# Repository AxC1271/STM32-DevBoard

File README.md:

# STM32 MCU Board

## 📖 Introduction
This repository is my first ever PCB design project. After working on projects that involved more digital circuits and RTL scripting, I've always wanted to build my own boards, specifically FPGA boards. However, I want to start on something simpler so I can understand the inner workings of PCB design, decision choices, and general concepts that are crucial to a functional STM32 board.

## 🛠️ Design Approach
Given that this is just a basic guide to designing, laying out, and manufacturing a simple STM32 board, this PCB will only offer a single USB port, an I2C interface, an SWD interface, and a UART interface. The specific processor chip that we are using is the STM32F103C8Tx, which uses an `ARM Cortex-M3 processor`. 

### ⚡ Power Regulator Circuit

<p align="center">
    <em> LDO-Based Power Regulator Circuit.</em>
</p>

Here we have the external USB-B micro port that interfaces with our STM32 microcontroller. In order to use `VBUS` coming from this port, I stepped down any input voltage down to 3.3V using the **AMS1117** chip, which requires two `22uF` capacitors according to its datasheet, one at the input and one at the output. At the output, the 3.3V signal is then passed through an LED with a current limiting resistor as a visual indicator that the 3.3V source is present at the output.

<br />
Quick note about the shield option being ignored, generally the shield pin is to connect the board to an external chassis but because this is a standalone board, that's why it's ignored.

### 🔲 STM32F103C8T6 MCU

<p align="center">
    <em>MCU Schematic with USB-B Micro Interface.</em>
</p>

First and foremost, there needs to be capacitors between the 3.3V source and ground. Since this specific STM32 microcontroller has 4 **VDD** pins, there must generally be a `100 nF` capacitor in parallel for each of these pins. These capacitors act as `decoupling capacitors`, ensuring a steady voltage supply to each VDD pin. In addition, a bulk capacitor with a value of `4.7 uF` is also placed in parallel to the decoupling capacitors to handle lower-frequency current swings, while the decoupling capacitors handle the higher frequency noise and transients.

## 🧩 PCB Layout

<p align="center">
    <em> Signal traces on the STM32 board, with power traces being 0.5mm while ordinary traces are kept at 0.3mm. Vias are used for ground traces. </em>
</p>

In general, vias are used to link ground pins to the ground plane. Most signals are routed on the top copper layer, with a couple of vias used to prevent signal crossing especially with the 3.3V bus. 
A copper pour was used near the voltage regulator to create ground and power planes whilst also reducing EMI and improving signal integrity.

Quick note: to further increase the stability of a 2-layer board like this, it is recommended to add as much stitching vias as possible, on top of adding a ground pour on the top layer. This is to decrease
the distance that sensitive signals have to travel to get to ground, reducing the inductance and therefore maximizing signal integrity.

## 🖼️ 3D View

<p align="center">
    <em> Front copper layer with all signal traces and silkscreens. </em>
</p>

## 🧪 Physical Board / Functionality

After passing a design rule check on KiCAD, it's time to send the files to a PCB manufacturer to get my board assembled. For this specific board, I'm using `JLCPCB`'s services to get my board manufactured. 

<p align="center">
    <em>Manufactured Board from JLCPCB.</em>
</p>

Unfortunately, I was unable to find the USB micro-B ports for these boards, but I still want to be able to program it using an ST-Linker that I found off of Amazon for roughly `$9`. 

## 💻 Code

To test the UART interface of this STM32 board, I'll write a simple UART transceiver on my Basys3 FPGA board to interface with it.

UART Receiver:
```VHDL
library IEEE;
use IEEE.STD_LOGIC_1164.ALL;
use IEEE.NUMERIC_STD.ALL;

entity uart_rx is
    generic (
        clk_ticks: integer := 54 -- taken from (100_000_000 / 115200) / 16 = 54.25 ticks
        );
    port ( 
        clk : in STD_LOGIC;
        rst : in STD_LOGIC;
        rx : in STD_LOGIC;
        byte : out STD_LOGIC_VECTOR (7 downto 0);
        write : out STD_LOGIC
        );
end uart_rx;

architecture Behavioral of uart_rx is
    -- define internal signals here
    type rx_state is (IDLE, START, DATA, STOP); -- defined states
    signal curr_state : rx_state := IDLE; -- initial state
    
    signal baud_clk : STD_LOGIC := '0';
    signal byte_i : STD_LOGIC_VECTOR(7 downto 0) := (others => '0');
    
begin
    -- define internal processes here
    
    -- first process is a clock generator that generates an oversampled
    -- clock signal to check for the rx signal
    clk_generator : process(clk, rst) 
        variable clk_count : integer range 0 to clk_ticks := 0;
    begin 
        if rst = '1' then
            clk_count := 0;
            baud_clk <= '0';
        elsif rising_edge(clk) then
            if clk_count = clk_ticks then
                clk_count := 0;
                baud_clk <= '1'; -- set high when clk count reaches 54
            else
                clk_count := clk_count + 1;
                baud_clk <= '0';
            end if;
        end if;
    end process;
    
    -- second process handles the state machine logic
    rx_FSM : process(clk, rst) 
        variable bit_count : integer range 0 to 7 := 0; -- check for where we are in the data word
        variable bit_duration : integer range 0 to 15 := 0; -- check if a logic level has stayed steady
    begin
        if rst = '1' then
            byte_i <= (others => '0'); -- reset data bus
            curr_state <= IDLE;
            bit_count := 0;
            bit_duration := 0;
            write <= '0';
        elsif rising_edge(clk) then
            if baud_clk = '1' then
                case curr_state is
                    when IDLE =>
                        byte_i <= (others => '0');
                        bit_count := 0;
                        bit_duration := 0;
                        write <= '0';
                        -- if the rx line gets pulled low then
                        if rx = '0' then
                            curr_state <= START;
                        end if;
                    when START =>
                        write <= '0';
                        if rx = '0' then
                            if bit_duration = 7 then
                                curr_state <= DATA;
                                bit_duration := 0;
                            else
                                bit_duration := bit_duration + 1;
                            end if;
                        else
                            curr_state <= IDLE;
                        end if;
                    when DATA =>
                        write <= '0';
                        if (bit_duration = 15) then                
                                byte_i(bit_count) <= rx;     
                                bit_duration := 0;
                                if (bit_count = 7) then -- we got 8 bits             
                                    curr_state <= STOP;
                                    bit_duration := 0;
                                else
                                    bit_count := bit_count + 1;
                                end if;
                            else
                                bit_duration := bit_duration + 1;
                            end if;
                    when STOP =>
                        if (bit_duration = 15) then      
                            if rx = '1' then  -- validate stop bit is HIGH
                                byte <= byte_i;
                                write <= '1';    
                                curr_state <= IDLE;
                            else
                            -- Invalid stop bit, frame error - reset
                                curr_state <= IDLE;
                            end if;
                        else
                            bit_duration := bit_duration + 1;
                        end if;
                    when others =>
                        curr_state <= IDLE;
                end case;
            end if;
        end if;
    end process;

end Behavioral;
```

Now we can write the C++ code for the STM32 to pass in some serial data to the Basys3 board and vice versa. We will interface using PlatformIO and write some firmware for the STM32 to transmit some characters to the FPGA. This is just one test code example:

```C++
#include <Arduino.h>
#include <HardwareSerial.h>

// TX pin: PB6, RX pin: PB7 (for UART1)
HardwareSerial Serial1(PB7, PB6); // RX, TX pins

unsigned long lastByteTime = 0;
const unsigned long byteInterval = 1000; // send each byte every 1 second
const char message[] = "Hello "; // message to send
int currentByteIndex = 0;
const int messageLength = 6; 

void setup() {
  Serial1.begin(115200); // uart receiver has baud rate of 115200
  
  Serial.begin(115200);
  Serial.println("STM32 UART Transmitter Started");
  Serial.println("Transmitting 'Hello' - one byte per second");

}

void loop() {
  if (millis() - lastByteTime >= byteInterval) {
    
    char currentByte = message[currentByteIndex];
    Serial1.write(currentByte);
    
    Serial.print("Transmitted byte: '");
    Serial.print(currentByte);
    Serial.print("' (ASCII: ");
    Serial.print((int)currentByte);
    Serial.println(")");

    digitalWrite(PC13, !digitalRead(PC13));
    
    currentByteIndex++;
    if (currentByteIndex >= messageLength) {
      currentByteIndex = 0; 
      Serial.println("--- Message complete, restarting ---");
    }
    
    lastByteTime = millis();
  }
  
  delay(10);
}
```

## 🎥 Video Demo

The first **[video demo](https://youtube.com/shorts/mgw7LnCIHqA)**  shows the FPGA receiver interacting with my Macbook via the `USB-to-Serial bridge`. The purpose of this
is to see the board behaving correctly from a known source using the terminal. Once the receiver's behavior has been validated,
then we can integrate the STM32 board and test its functionality.

Here's the **[video demo](https://youtube.com/shorts/DqSGexJcCeM)** showing the Basys3 taking the data bytes through a PMOD port from the STM32 MCU board to show that communication is 
indeed possible from my fabricated board. This required changing the RX pin on the FPGA to receive the byte.

---

Thanks for stopping and reading until the very end and I hope you learned something new from this README file!

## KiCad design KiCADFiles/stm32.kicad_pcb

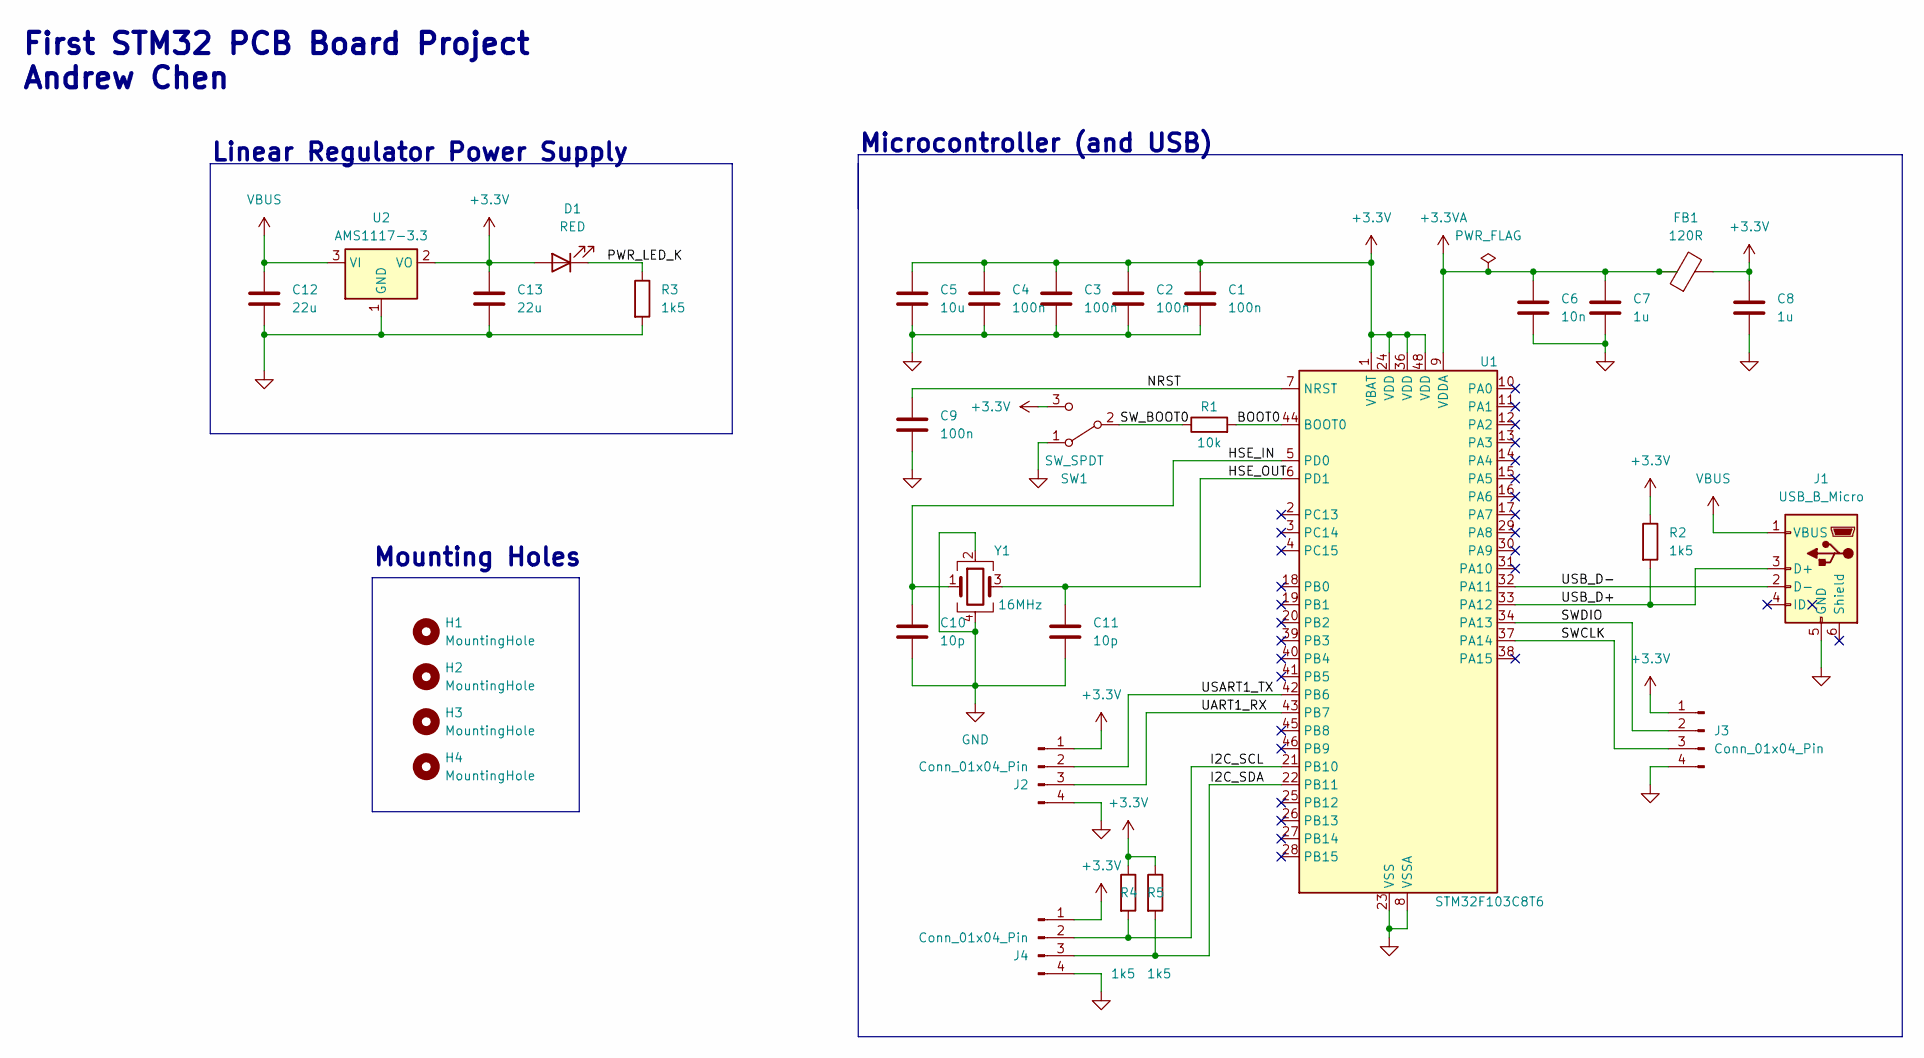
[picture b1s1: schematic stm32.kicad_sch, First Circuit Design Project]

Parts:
C1, C2, C3, C4, C9: 100n; C_0402_1005Metric
C5: 10u; C_0603_1608Metric
C6: 10n; C_0402_1005Metric
C7, C8: 1u; C_0402_1005Metric
C10, C11: 10p; C_0402_1005Metric
C12, C13: 22u; C_0805_2012Metric
D1: RED; LED_0603_1608Metric
FB1: 120R; L_0603_1608Metric
H1, H2, H3, H4: MountingHole; MountingHole_2.2mm_M2
J1: USB_B_Micro; USB_Micro-B_Wuerth_629105150521
J2, J3, J4: Conn_01x04_Pin; PinHeader_1x04_P2.54mm_Vertical
R1: 10k; R_0402_1005Metric
R2, R3, R4, R5: 1k5; R_0402_1005Metric
SW1: SW_SPDT; SW_SPDT_PCM12
U1: STM32F103C8T6; LQFP-48_7x7mm_P0.5mm
U2: AMS1117-3.3; SOT-223-3_TabPin2
Y1: 16MHz; Crystal_SMD_3225-4Pin_3.2x2.5mm

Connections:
+3.3V: C1.1, C2.1, C3.1, C4.1, C5.1, C8.1, C13.1, D1.2 (A), FB1.2, J2.1, J3.1, J4.1, R2.1, R4.1, R5.1, SW1.3 (C), U1.1 (VBAT), U1.24 (VDD), U1.36 (VDD), U1.48 (VDD), U2.2 (VO)
+3.3VA: C6.1, C7.1, FB1.1, U1.9 (VDDA)
/BOOT0: R1.2, U1.44 (BOOT0)
/HSE_IN: C10.1, U1.5 (PD0), Y1.1
/HSE_OUT: C11.1, U1.6 (PD1), Y1.3
/I2C_SCL: J4.2, R4.2, U1.21 (PB10)
/I2C_SDA: J4.3, R5.2, U1.22 (PB11)
/NRST: C9.1, U1.7 (NRST)
/PWR_LED_K: D1.1 (K), R3.1
/SWCLK: J3.3, U1.37 (PA14)
/SWDIO: J3.2, U1.34 (PA13)
/SW_BOOT0: R1.1, SW1.2 (B)
/UART1_RX: J2.3, U1.43 (PB7)
/USART1_TX: J2.2, U1.42 (PB6)
/USB_D+: J1.3 (D+), R2.2, U1.33 (PA12)
/USB_D-: J1.2 (D-), U1.32 (PA11)
GND: C1.2, C2.2, C3.2, C4.2, C5.2, C6.2, C7.2, C8.2, C9.2, C10.2, C11.2, C12.2, C13.2, J1.5 (GND), J2.4, J3.4, J4.4, R3.2, SW1.1 (A), U1.8 (VSSA), U1.23 (VSS), U1.35 (VSS), U1.47 (VSS), U2.1 (GND), Y1.2, Y1.4
VBUS: C12.1, J1.1 (VBUS), U2.3 (VI)

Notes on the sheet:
Mounting Holes
Microcontroller (and USB)
Linear Regulator Power Supply
First STM32 PCB Board Project Andrew Chen

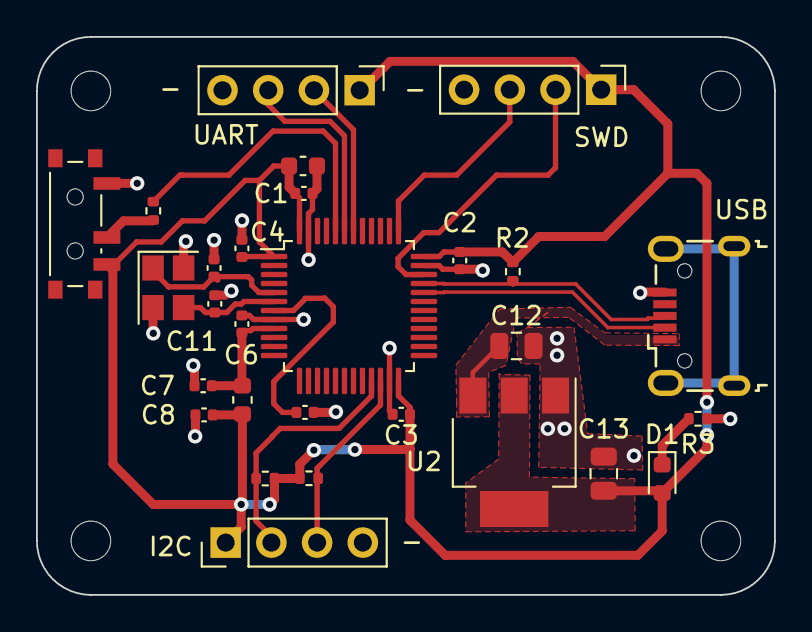
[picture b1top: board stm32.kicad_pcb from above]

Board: 2 copper layers, 41.0 x 31.0 mm, 32 parts (0 on the bottom side), 18 nets.

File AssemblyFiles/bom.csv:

Comment,Designator,Footprint,LCSC Part #,Quantity
100nF,C1 C2 C3 C4 C9,C_0402_1005Metric,C1525,5
10uF,C5,C_0603_1608Metric,C19702,1
10nF,C6,C_0402_1005Metric,C15195,1
1uF,C7 C8,C_0402_1005Metric,C52923,2
10pF,C10 C11,C_0402_1005Metric,C32949,2
22uF,C12 C13,C_0805_2012Metric,C45783,2
RED LED,D1,LED_0603_1608Metric,C2286,1
120R@100MHz Ferrite Bead,FB1,L_0603_1608Metric,C1030,1
USB Micro-B,J1,USB_Micro-B_Wuerth_629105150521,C132563,1
1x4 2.54mm Pin Header,J2 J3 J4,PinHeader_1x04_P2.54mm_Vertical,C124378,3
10kΩ,R1,R_0402_1005Metric,C25744,1
1.5kΩ,R2 R3 R4 R5,R_0402_1005Metric,C25867,4
SPDT Slide Switch,SW1,SW_SPDT_PCM12,C221841,1
STM32F103C8T6,U1,LQFP-48_7x7mm_P0.5mm,C8734,1
AMS1117-3.3V,U2,SOT-223-3_TabPin2,C6186,1
16MHz Crystal 4-pin,Y1,Crystal_SMD_3225-4Pin_3.2x2.5mm,C13738,1

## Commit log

2025-07-30 Centered Imaging
2025-07-31 Rename MCUSchematic.png to STMSchematic.png
2025-07-31 Rename TPS54300DDA_Datasheet.png to TPS5430DDA_Datasheet.png
2025-08-14 Update README.md
    Image ratio should be fixed later for better looking documentation
2025-08-17 Rename main.c to helloworld.c
2025-09-22 Rename uart_rx.v to uart_rx.vhd
2025-10-31 Implement ASCII to SSD decoder in VHDL
2025-10-31 Implement UART receiver in VHDL
2025-10-31 Convert UART receiver from Verilog to VHDL
    Updated UART receiver implementation from Verilog to VHDL, including state machine and clock generator processes.
